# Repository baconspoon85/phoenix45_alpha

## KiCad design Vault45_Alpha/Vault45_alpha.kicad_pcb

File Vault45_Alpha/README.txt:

This directory contains a Lagacy Vault 45 compatible version of the Phoenix 45 Alpha PCB.
The schematic mostly the same except for a few layout options: The shift key options were removed. Make sure you have two 1.5u R4 caps. Several bottom row options were also removed and adjusted to avoid interference with mounting screws and posts. 2u spacebars were added with stabilizer support. It may not be possible to have stabilizers and the encoder option together in the same build configuration. There is a KLE in this directory showing just the bottom row options. No matrix positions have been added or removed. All other changes are to component positions and edge cuts, meaning the BOM and firmware for the Phoenix 45 version are compatible. You will need separate position files and gerbers generated from this project file. Those are included in the Fabrication directory. Additionally, since both boards are mounted via the plate, the custom plate is needed. There is a seperate project file containing the plate outline as a DXF file, as well as a KiCad project directory containing fabrication files for an FR4 plate.

Firmware was stripped down from original galvy fork:
https://github.com/galvy0/qmk_firmware/tree/galvy/keyboards/galvy/jd45_alpha

...to fit vial:
https://github.com/baconspoon85/vial-qmk/tree/vial/keyboards/baconspoon85/vault45_alpha

Vial and default QMK hex files are in the "Firmware" directory.

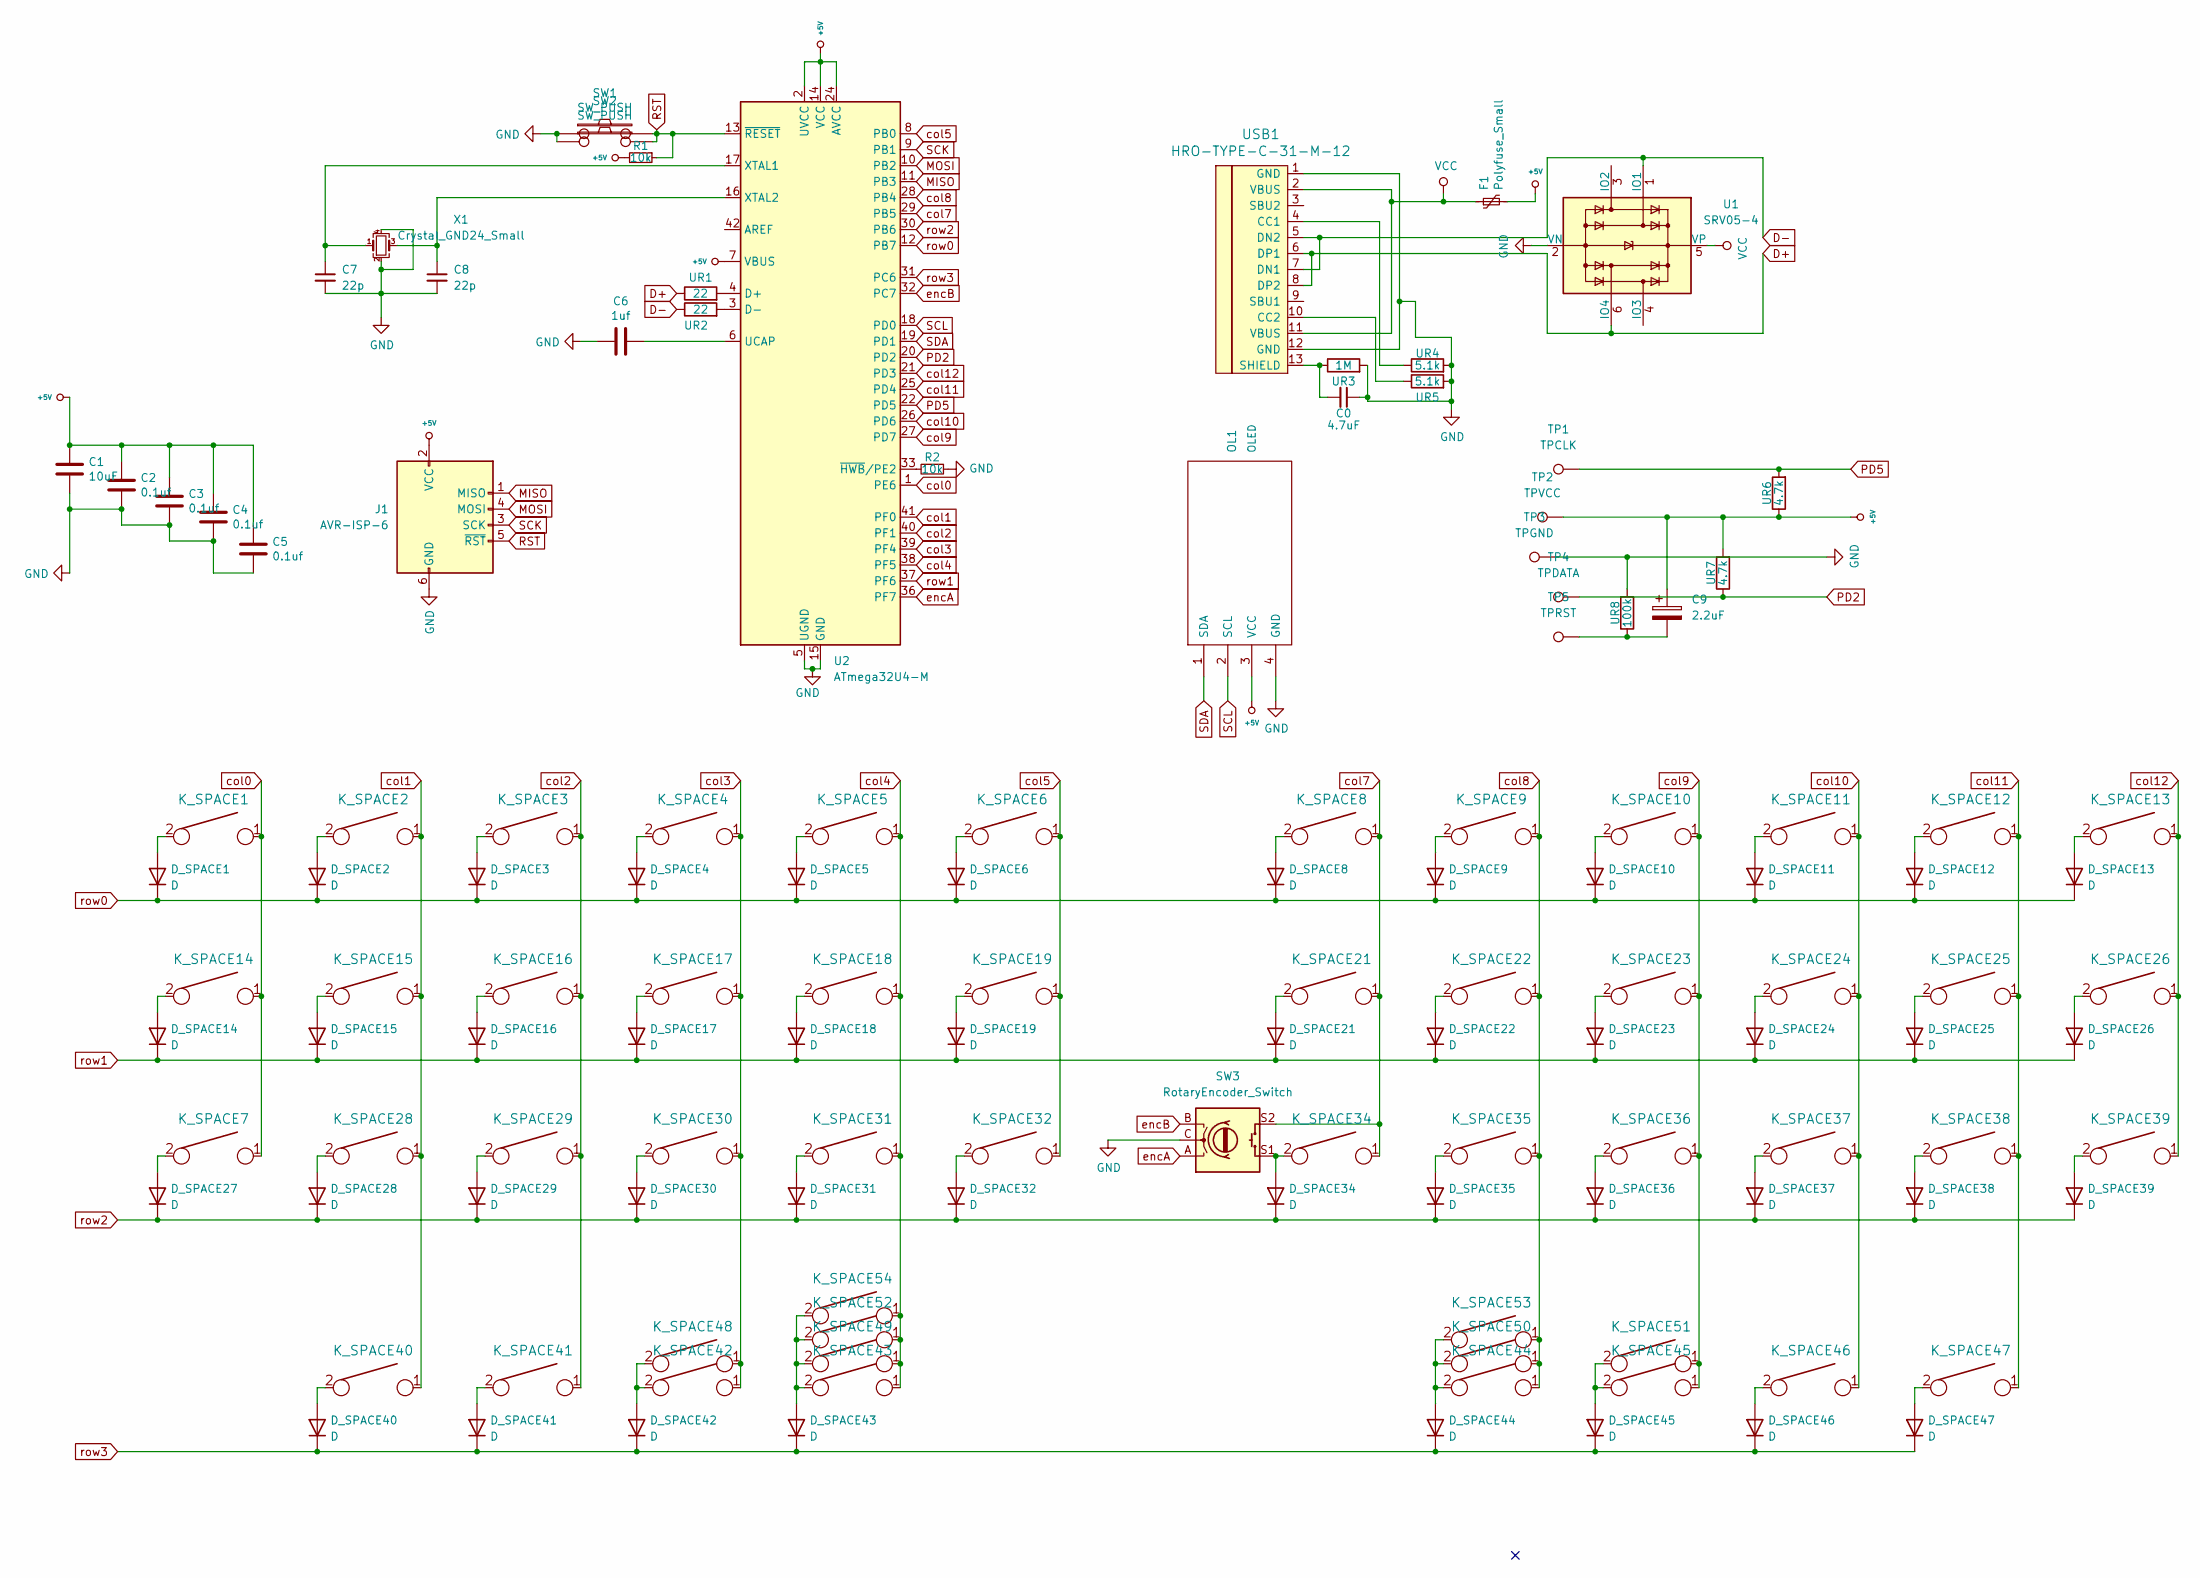
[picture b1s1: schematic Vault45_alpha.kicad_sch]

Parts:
C0: 4.7uF; C_0805_2012Metric_Pad1.18x1.45mm_HandSolder
C1: 10uF; C_0805_2012Metric_Pad1.18x1.45mm_HandSolder
C2, C3, C4, C5: 0.1uf; C_0805_2012Metric_Pad1.18x1.45mm_HandSolder
C6: 1uf; C_0805_2012Metric_Pad1.18x1.45mm_HandSolder
C7, C8: 22p; C_0805_2012Metric_Pad1.18x1.45mm_HandSolder
C9: 2.2uF; C_0805_2012Metric_Pad1.18x1.45mm_HandSolder
D_SPACE1, D_SPACE2, D_SPACE3, D_SPACE4, D_SPACE5, D_SPACE6, D_SPACE8, D_SPACE9, D_SPACE10, D_SPACE11, D_SPACE12, D_SPACE13, D_SPACE14, D_SPACE15, D_SPACE16, D_SPACE17, D_SPACE18, D_SPACE19, D_SPACE21, D_SPACE22, D_SPACE23, D_SPACE24, D_SPACE25, D_SPACE26, D_SPACE27, D_SPACE28, D_SPACE29, D_SPACE30, D_SPACE31, D_SPACE32, D_SPACE34, D_SPACE35, D_SPACE36, D_SPACE37, D_SPACE38, D_SPACE39, D_SPACE40, D_SPACE41, D_SPACE42, D_SPACE43, D_SPACE44, D_SPACE45, D_SPACE46, D_SPACE47: D; D_SOD-123
F1: Polyfuse_Small; Fuse_1206_3216Metric_Pad1.42x1.75mm_HandSolder
J1: AVR-ISP-6; IDC-Header_2x03_P2.54mm_Vertical
K_SPACE1, K_SPACE2, K_SPACE3, K_SPACE4, K_SPACE5, K_SPACE6, K_SPACE8, K_SPACE9, K_SPACE10, K_SPACE11, K_SPACE12, K_SPACE13, K_SPACE14, K_SPACE15, K_SPACE16, K_SPACE17, K_SPACE18, K_SPACE19, K_SPACE21, K_SPACE22, K_SPACE23, K_SPACE24, K_SPACE25, K_SPACE26, K_SPACE28, K_SPACE29, K_SPACE30, K_SPACE31, K_SPACE32, K_SPACE34, K_SPACE35, K_SPACE36, K_SPACE37, K_SPACE38, K_SPACE40, K_SPACE47, K_SPACE48, K_SPACE51: KEYSW; MXOnly-1U-NoLED
K_SPACE7, K_SPACE39: KEYSW; MXOnly-1.5U-NoLED
K_SPACE41, K_SPACE42, K_SPACE45, K_SPACE46: KEYSW; MXOnly-1.25U-NoLED
K_SPACE43, K_SPACE44: KEYSW; MXOnly-1.75U-NoLED
K_SPACE49, K_SPACE50: KEYSW; MXOnly-2U-ReversedStabilizers-NoLED
K_SPACE52, K_SPACE53: KEYSW; MXOnly-3U-ReversedStabilizers-NoLED
K_SPACE54: KEYSW; MXOnly-4U-ReversedStabilizers-NoLED
OL1: OLED; OLED_v2
R1, R2: 10k; R_0805_2012Metric_Pad1.20x1.40mm_HandSolder
SW1, SW2: SW_PUSH; SW_SPST_SKQG_WithoutStem
SW3: RotaryEncoder_Switch; RotaryEncoder_Alps_EC11E-Switch_Vertical_H20mm
TP1: TPCLK; TestPoint_THTPad_1.0x1.0mm_Drill0.5mm
TP2: TPVCC; TestPoint_THTPad_1.0x1.0mm_Drill0.5mm
TP3: TPGND; TestPoint_THTPad_1.0x1.0mm_Drill0.5mm
TP4: TPDATA; TestPoint_THTPad_1.0x1.0mm_Drill0.5mm
TP5: TPRST; TestPoint_THTPad_1.0x1.0mm_Drill0.5mm
U1: SRV05-4; SOT-23-6_Handsoldering
U2: ATmega32U4-M; QFN-44-1EP_7x7mm_P0.5mm_EP5.2x5.2mm_ThermalVias
UR1, UR2: 22; R_0805_2012Metric_Pad1.20x1.40mm_HandSolder
UR3: 1M; R_0805_2012Metric_Pad1.20x1.40mm_HandSolder
UR4, UR5: 5.1k; R_0805_2012Metric_Pad1.20x1.40mm_HandSolder
UR6, UR7: 4.7k; R_0805_2012Metric_Pad1.20x1.40mm_HandSolder
UR8: 100k; R_0805_2012Metric_Pad1.20x1.40mm_HandSolder
USB1: HRO-TYPE-C-31-M-12; HRO-TYPE-C-31-M-12-HandSoldering
X1: Crystal_GND24_Small; Crystal_SMD_3225-4Pin_3.2x2.5mm_HandSoldering

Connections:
+5V: C1.1, C2.1, C3.1, C4.1, C5.1, C9.1, F1.2, J1.2 (VCC), OL1.3 (VCC), R1.2, TP2.1, U2.2 (UVCC), U2.7 (VBUS), U2.14 (VCC), U2.24 (AVCC), U2.34 (VCC), U2.44 (AVCC), UR6.1, UR7.2
D+: U1.6 (IO4), UR2.1, USB1.6 (DP1), USB1.8 (DP2)
D-: U1.1 (IO1), UR1.1, USB1.5 (DN2), USB1.7 (DN1)
GND: C0.1, C1.2, C2.2, C3.2, C4.2, C5.2, C6.2, C7.2, C8.2, J1.6 (GND), OL1.4 (GND), R2.1, SW1.1, SW2.1, SW3.C, TP3.1, U1.2 (VN), U2.5 (UGND), U2.15 (GND), U2.23 (GND), U2.35 (GND), U2.43 (GND), U2.45 (GND), UR3.2, UR4.2, UR5.2, UR8.2, USB1.1 (GND), USB1.12 (GND), X1.2, X1.4
MISO: J1.1 (MISO), U2.11 (PB3)
MOSI: J1.4 (MOSI), U2.10 (PB2)
unnamed: C9.2, TP5.1, UR8.1
unnamed: D_SPACE1.2 (A), K_SPACE1.2
unnamed: D_SPACE2.2 (A), K_SPACE2.2
unnamed: D_SPACE3.2 (A), K_SPACE3.2
unnamed: D_SPACE4.2 (A), K_SPACE4.2
unnamed: D_SPACE5.2 (A), K_SPACE5.2
unnamed: D_SPACE6.2 (A), K_SPACE6.2
unnamed: D_SPACE8.2 (A), K_SPACE8.2
unnamed: D_SPACE9.2 (A), K_SPACE9.2
unnamed: D_SPACE10.2 (A), K_SPACE10.2
unnamed: D_SPACE11.2 (A), K_SPACE11.2
unnamed: D_SPACE12.2 (A), K_SPACE12.2
unnamed: D_SPACE13.2 (A), K_SPACE13.2
unnamed: D_SPACE14.2 (A), K_SPACE14.2
unnamed: D_SPACE15.2 (A), K_SPACE15.2
unnamed: D_SPACE16.2 (A), K_SPACE16.2
unnamed: D_SPACE17.2 (A), K_SPACE17.2
unnamed: D_SPACE18.2 (A), K_SPACE18.2
unnamed: D_SPACE19.2 (A), K_SPACE19.2
unnamed: D_SPACE21.2 (A), K_SPACE21.2
unnamed: D_SPACE22.2 (A), K_SPACE22.2
unnamed: D_SPACE23.2 (A), K_SPACE23.2
unnamed: D_SPACE24.2 (A), K_SPACE24.2
unnamed: D_SPACE25.2 (A), K_SPACE25.2
unnamed: D_SPACE26.2 (A), K_SPACE26.2
unnamed: D_SPACE27.2 (A), K_SPACE7.2
unnamed: D_SPACE28.2 (A), K_SPACE28.2
unnamed: D_SPACE29.2 (A), K_SPACE29.2
unnamed: D_SPACE30.2 (A), K_SPACE30.2
unnamed: D_SPACE31.2 (A), K_SPACE31.2
unnamed: D_SPACE32.2 (A), K_SPACE32.2
unnamed: D_SPACE34.2 (A), K_SPACE34.2, SW3.S1
unnamed: D_SPACE35.2 (A), K_SPACE35.2
unnamed: D_SPACE36.2 (A), K_SPACE36.2
unnamed: D_SPACE37.2 (A), K_SPACE37.2
unnamed: D_SPACE38.2 (A), K_SPACE38.2
unnamed: D_SPACE39.2 (A), K_SPACE39.2
unnamed: D_SPACE40.2 (A), K_SPACE40.2
unnamed: D_SPACE41.2 (A), K_SPACE41.2
unnamed: D_SPACE42.2 (A), K_SPACE42.2, K_SPACE48.2
unnamed: D_SPACE43.2 (A), K_SPACE43.2, K_SPACE49.2, K_SPACE52.2, K_SPACE54.2
unnamed: D_SPACE44.2 (A), K_SPACE44.2, K_SPACE50.2, K_SPACE53.2
unnamed: D_SPACE45.2 (A), K_SPACE45.2, K_SPACE51.2
unnamed: D_SPACE46.2 (A), K_SPACE46.2
unnamed: D_SPACE47.2 (A), K_SPACE47.2
unnamed: U2.4 (D+), UR2.2
unnamed: U2.3 (D-), UR1.2
unnamed: C6.1, U2.6 (UCAP)
unnamed: C7.1, U2.17 (XTAL1), X1.1
unnamed: C8.1, U2.16 (XTAL2), X1.3
unnamed: R2.2, U2.33 (~HWB/PE2)
unnamed: UR4.1, USB1.4 (CC1)
unnamed: UR5.1, USB1.10 (CC2)
unnamed: C0.2, UR3.1, USB1.13 (SHIELD)
PD2: TP4.1, U2.20 (PD2), UR7.1
PD5: TP1.1, U2.22 (PD5), UR6.2
RST: J1.5 (~RST), R1.1, SW1.2, SW2.2, U2.13 (~RESET)
SCK: J1.3 (SCK), U2.9 (PB1)
SCL: OL1.2 (SCL), U2.18 (PD0)
SDA: OL1.1 (SDA), U2.19 (PD1)
VCC: F1.1, U1.5 (VP), USB1.2 (VBUS), USB1.11 (VBUS)
col0: K_SPACE1.1, K_SPACE7.1, K_SPACE14.1, U2.1 (PE6)
col1: K_SPACE2.1, K_SPACE15.1, K_SPACE28.1, K_SPACE40.1, U2.41 (PF0)
col2: K_SPACE3.1, K_SPACE16.1, K_SPACE29.1, K_SPACE41.1, U2.40 (PF1)
col3: K_SPACE4.1, K_SPACE17.1, K_SPACE30.1, K_SPACE42.1, K_SPACE48.1, U2.39 (PF4)
col4: K_SPACE5.1, K_SPACE18.1, K_SPACE31.1, K_SPACE43.1, K_SPACE49.1, K_SPACE52.1, K_SPACE54.1, U2.38 (PF5)
col5: K_SPACE6.1, K_SPACE19.1, K_SPACE32.1, U2.8 (PB0)
col7: K_SPACE8.1, K_SPACE21.1, K_SPACE34.1, SW3.S2, U2.29 (PB5)
col8: K_SPACE9.1, K_SPACE22.1, K_SPACE35.1, K_SPACE44.1, K_SPACE50.1, K_SPACE53.1, U2.28 (PB4)
col9: K_SPACE10.1, K_SPACE23.1, K_SPACE36.1, K_SPACE45.1, K_SPACE51.1, U2.27 (PD7)
col10: K_SPACE11.1, K_SPACE24.1, K_SPACE37.1, K_SPACE46.1, U2.26 (PD6)
col11: K_SPACE12.1, K_SPACE25.1, K_SPACE38.1, K_SPACE47.1, U2.25 (PD4)
col12: K_SPACE13.1, K_SPACE26.1, K_SPACE39.1, U2.21 (PD3)
encA: SW3.A, U2.36 (PF7)
encB: SW3.B, U2.32 (PC7)
row0: D_SPACE1.1 (K), D_SPACE2.1 (K), D_SPACE3.1 (K), D_SPACE4.1 (K), D_SPACE5.1 (K), D_SPACE6.1 (K), D_SPACE8.1 (K), D_SPACE9.1 (K), D_SPACE10.1 (K), D_SPACE11.1 (K), D_SPACE12.1 (K), D_SPACE13.1 (K), U2.12 (PB7)
row1: D_SPACE14.1 (K), D_SPACE15.1 (K), D_SPACE16.1 (K), D_SPACE17.1 (K), D_SPACE18.1 (K), D_SPACE19.1 (K), D_SPACE21.1 (K), D_SPACE22.1 (K), D_SPACE23.1 (K), D_SPACE24.1 (K), D_SPACE25.1 (K), D_SPACE26.1 (K), U2.37 (PF6)
row2: D_SPACE27.1 (K), D_SPACE28.1 (K), D_SPACE29.1 (K), D_SPACE30.1 (K), D_SPACE31.1 (K), D_SPACE32.1 (K), D_SPACE34.1 (K), D_SPACE35.1 (K), D_SPACE36.1 (K), D_SPACE37.1 (K), D_SPACE38.1 (K), D_SPACE39.1 (K), U2.30 (PB6)
row3: D_SPACE40.1 (K), D_SPACE41.1 (K), D_SPACE42.1 (K), D_SPACE43.1 (K), D_SPACE44.1 (K), D_SPACE45.1 (K), D_SPACE46.1 (K), D_SPACE47.1 (K), U2.31 (PC6)

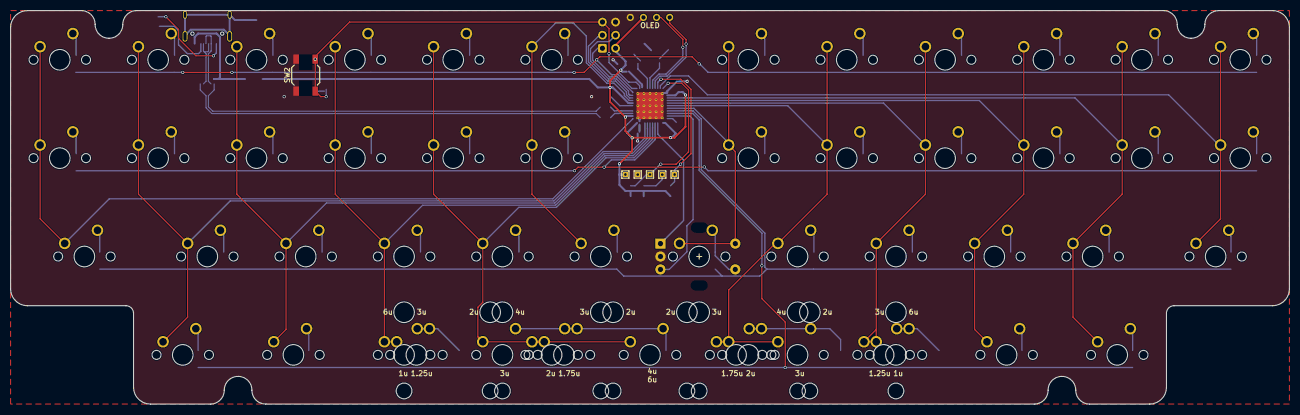
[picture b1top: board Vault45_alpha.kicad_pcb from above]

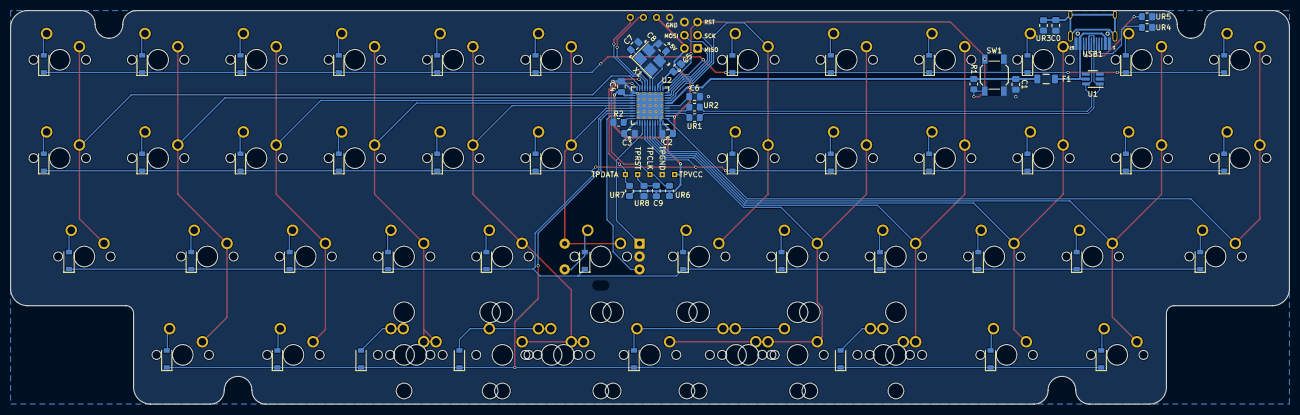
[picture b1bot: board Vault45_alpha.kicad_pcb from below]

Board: 2 copper layers, 247.7 x 76.2 mm, 130 parts (71 on the bottom side), 85 nets.

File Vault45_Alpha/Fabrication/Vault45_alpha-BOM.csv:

Designator,Footprint,Comment,JLCPCB Part#(optional)
C0,C_0805_2012Metric_Pad1.18x1.45mm_HandSolder,4.7uF,
C1,C_0805_2012Metric_Pad1.18x1.45mm_HandSolder,10uF,
C2,C_0805_2012Metric_Pad1.18x1.45mm_HandSolder,0.1uf,
C3,C_0805_2012Metric_Pad1.18x1.45mm_HandSolder,0.1uf,
C4,C_0805_2012Metric_Pad1.18x1.45mm_HandSolder,0.1uf,
C5,C_0805_2012Metric_Pad1.18x1.45mm_HandSolder,0.1uf,
C6,C_0805_2012Metric_Pad1.18x1.45mm_HandSolder,1uf,
C7,C_0805_2012Metric_Pad1.18x1.45mm_HandSolder,22p,
C8,C_0805_2012Metric_Pad1.18x1.45mm_HandSolder,22p,
C9,C_0805_2012Metric_Pad1.18x1.45mm_HandSolder,2.2uF,
D_SPACE1,D_SOD-123,1N4148W,C81598
D_SPACE10,D_SOD-123,1N4148W,C81598
D_SPACE11,D_SOD-123,1N4148W,C81598
D_SPACE12,D_SOD-123,1N4148W,C81598
D_SPACE13,D_SOD-123,1N4148W,C81598
D_SPACE14,D_SOD-123,1N4148W,C81598
D_SPACE15,D_SOD-123,1N4148W,C81598
D_SPACE16,D_SOD-123,1N4148W,C81598
D_SPACE17,D_SOD-123,1N4148W,C81598
D_SPACE18,D_SOD-123,1N4148W,C81598
D_SPACE19,D_SOD-123,1N4148W,C81598
D_SPACE2,D_SOD-123,1N4148W,C81598
D_SPACE21,D_SOD-123,1N4148W,C81598
D_SPACE22,D_SOD-123,1N4148W,C81598
D_SPACE23,D_SOD-123,1N4148W,C81598
D_SPACE24,D_SOD-123,1N4148W,C81598
D_SPACE25,D_SOD-123,1N4148W,C81598
D_SPACE26,D_SOD-123,1N4148W,C81598
D_SPACE27,D_SOD-123,1N4148W,C81598
D_SPACE28,D_SOD-123,1N4148W,C81598
D_SPACE29,D_SOD-123,1N4148W,C81598
D_SPACE3,D_SOD-123,1N4148W,C81598
D_SPACE30,D_SOD-123,1N4148W,C81598
D_SPACE31,D_SOD-123,1N4148W,C81598
D_SPACE32,D_SOD-123,1N4148W,C81598
D_SPACE34,D_SOD-123,1N4148W,C81598
D_SPACE35,D_SOD-123,1N4148W,C81598
D_SPACE36,D_SOD-123,1N4148W,C81598
D_SPACE37,D_SOD-123,1N4148W,C81598
D_SPACE38,D_SOD-123,1N4148W,C81598
D_SPACE39,D_SOD-123,1N4148W,C81598
D_SPACE4,D_SOD-123,1N4148W,C81598
D_SPACE40,D_SOD-123,1N4148W,C81598
D_SPACE41,D_SOD-123,1N4148W,C81598
D_SPACE42,D_SOD-123,1N4148W,C81598
D_SPACE43,D_SOD-123,1N4148W,C81598
D_SPACE44,D_SOD-123,1N4148W,C81598
D_SPACE45,D_SOD-123,1N4148W,C81598
D_SPACE46,D_SOD-123,1N4148W,C81598
D_SPACE47,D_SOD-123,1N4148W,C81598
D_SPACE5,D_SOD-123,1N4148W,C81598
D_SPACE6,D_SOD-123,1N4148W,C81598
D_SPACE8,D_SOD-123,1N4148W,C81598
D_SPACE9,D_SOD-123,1N4148W,C81598
F1,Fuse_1206_3216Metric_Pad1.42x1.75mm_HandSolder,Polyfuse_Small,
R1,R_0805_2012Metric_Pad1.20x1.40mm_HandSolder,10k,
R2,R_0805_2012Metric_Pad1.20x1.40mm_HandSolder,10k,
SW1,SW_SPST_SKQG_WithoutStem,SW_PUSH,C318884
SW2,SW_SPST_SKQG_WithoutStem,SW_PUSH,C318884
U1,SOT-23-6_Handsoldering,SRV05-4,
U2,QFN-44-1EP_7x7mm_P0.5mm_EP5.2x5.2mm_ThermalVias,ATmega32U4-M,
UR1,R_0805_2012Metric_Pad1.20x1.40mm_HandSolder,22ohm,
UR2,R_0805_2012Metric_Pad1.20x1.40mm_HandSolder,22ohm,
UR3,R_0805_2012Metric_Pad1.20x1.40mm_HandSolder,1M,
UR4,R_0805_2012Metric_Pad1.20x1.40mm_HandSolder,5.1k,
UR5,R_0805_2012Metric_Pad1.20x1.40mm_HandSolder,5.1k,
UR6,R_0805_2012Metric_Pad1.20x1.40mm_HandSolder,4.7k,
UR7,R_0805_2012Metric_Pad1.20x1.40mm_HandSolder,4.7k,
UR8,R_0805_2012Metric_Pad1.20x1.40mm_HandSolder,100k,
USB1,HRO-TYPE-C-31-M-12-HandSoldering,HRO-TYPE-C-31-M-12,
X1,Crystal_SMD_3225-4Pin_3.2x2.5mm_HandSoldering,Crystal_GND24_Small,

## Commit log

2023-08-25 initial commit for vault45 version of phoenix45 alpha
2023-08-26 updated pcb layout to address interference with plate mounting hardware and added custom plate files
2023-08-26 added position file to Fabrication dir for Vault45 Alpha PCB
2023-09-03 Added bottom row options to Vault 45 Alpha PCB and updated fabrication files.
2023-09-03 Updated KLE JSON and PNG with additional bottom row spacebar options from previous commit (2x3u, 4u, and 6u).
2023-09-07 Updated plate DXF and FR4 KiCad project to accommodate all pottom row options on PCB
2023-09-07 Added BOM and POS files to Fabrication directory.Files are properly formatted for JLCPCB. BOM nets.
2023-09-07 Added kicad project file and gerbers for a plate with switch cutouts for 1u blockers or dummy switches in the center column instead of an OLED cutout. Added BOM to Vault45_Alpha/Fabrication dir, form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
2023-10-24 Update Vault45_alpha-BOM.csv
    Corrected part number for crystal. Original part number was for a 12MHz crystal. This needs to be a 16MHz crystal in the same SMD 3225 package.
2023-11-09 add vial and default qmk firmware for vault45_alpha
2023-11-09 update readme for firmware commit
2023-11-09 update vial hex for vault45_alpha
